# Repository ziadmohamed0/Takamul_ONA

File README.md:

<div align="center">

<br/>
<br/>

# Takamul iQ16 PLC

### Industrial IoT Controller — تكامل للحلول الذكية

<br/>

<br/>

> **Dual-core STM32F405 + ESP32-S3 · Supabase Multi-Tenant Cloud · Modbus RTU · DIN-Rail Mount**
> Designed for water treatment, flow control, and process automation in harsh industrial environments — engineered in Egypt 🇪🇬

</div>

---

## Table of Contents

- [Overview](#overview)
- [Key Features](#key-features)
- [System Architecture](#system-architecture)
- [Hardware](#hardware)
  - [PCB](#pcb--ona_hard)
  - [Mechanical Enclosure — V1](#mechanical-enclosure--v1)
  - [Mechanical Enclosure — V2](#mechanical-enclosure--v2)
- [Firmware](#firmware)
- [Cloud & Connectivity](#cloud--connectivity)
- [Repository Structure](#repository-structure)
- [Getting Started](#getting-started)
- [Supported Instruments](#supported-instruments)

---

## Overview

The **Takamul iQ16** is a compact, DIN-rail mounted industrial PLC built for real-world process automation. It pairs a **STM32F405RGT6** real-time controller — handling deterministic Modbus RTU field communication — with an **ESP32-S3** managing Wi-Fi, MQTT, and secure cloud telemetry via **Supabase Row-Level Security**.

Every unit ships ready to deploy: scan the MAC QR code on the box, link it to your account, and the device self-configures with zero manual setup.

**Built for:**
- Water treatment & desalination plants
- Flow metering systems (Endress+Hauser Promag P300)
- Multi-parameter water quality monitoring (TDS, pressure, temperature, differential)
- VFD pump control automation

---

## Key Features

| | Feature | Detail |
|---|---|---|
| ⚙️ | **Dual-Core Processing** | STM32F405RGT6 (real-time control) + ESP32-S3 (connectivity) |
| 📡 | **Field Protocols** | Modbus RTU × 2 ports (RS-485), bridged to cloud via MQTT |
| 🌊 | **Sensor Inputs** | Flow · Pressure · TDS · Temperature · Differential (5 channels) |
| ⚡ | **Actuator Outputs** | VFD Control × 2 (Variable Frequency Drive) |
| 🔋 | **Power Supply** | 12–24V DC wide-range input, onboard LM2596S regulator |
| 📶 | **Connectivity** | Wi-Fi 802.11 b/g/n, external SMA antenna, USB-C programming |
| ☁️ | **Cloud Backend** | Supabase PostgreSQL + RLS — multi-tenant, per-device data isolation |
| 🔐 | **Security** | JWT auth, RLS policies, NVS encrypted credential storage |
| 💡 | **Status Indicators** | Power · Run · Error · Comms · Wi-Fi (5 onboard LEDs) |
| 📦 | **Form Factor** | DIN-rail 35mm TS35, 3D-printable enclosure included |
| 🔌 | **Programming** | ST-LINK V2 (STM32) + USB-C ESP-IDF (ESP32) |
| 📋 | **Zero-Config** | MAC-based QR pairing — no manual IP or credential entry |

---

## System Architecture

```
┌─────────────────────────────────────────────────────────┐
│                    Field Instruments                     │
│  [Flow Meter]  [Pressure]  [TDS]  [Temp]  [Diff]       │
└──────────────────────┬──────────────────────────────────┘
                       │ Modbus RTU (RS-485)
              ┌────────▼────────┐
              │   STM32F405     │  ← Real-time deterministic control
              │  Modbus Master  │  ← VFD pump output control
              │  FreeRTOS       │
              └────────┬────────┘
                       │ UART (115200 baud)
              ┌────────▼────────┐
              │    ESP32-S3     │  ← Wi-Fi / MQTT / Cloud
              │  WifiManager    │
              │  SupabaseClient │──────────► Supabase Cloud
              │  MqttManager    │              (PostgreSQL + RLS)
              │  TelemetryMgr   │
              │  WebServer      │──────────► Local Config Portal
              │  NVSManager     │
              └─────────────────┘
```

---

## Hardware

### PCB — `ONA_HARD/`

The iQ16 PCB is a **4-layer board** designed in KiCad 7. The stackup separates power planes from signal layers to ensure clean analog sensor readings alongside noisy RS-485 and switching regulator circuits.

| Spec | Value |
|---|---|
| Layers | 4 (F.Cu · In1.Cu · In2.Cu · B.Cu) |
| MCUs | STM32F405RGT6 + ESP32-S3 module |
| Power | LM2596S buck converter, 220µF/35V + 100µF/50V bulk caps |
| RS-485 | Dual Modbus ports (ModBus 1: A/B, ModBus 2: Y/Z) |
| Programming | USB-C (ESP32) + ST-Link header (STM32) |
| Mounting | 4× M3 corner holes for DIN-rail clip assembly |
| Design tool | KiCad 7 |
| Fabrication | Gerber + drill files ready (JLCPCB / PCBWay) |

<table>
  <tr>
    <td align="center" width="50%">
      
      <br/><sub><b>iQ16 — DIN-Rail Mounted</b></sub>
    </td>
    <td align="center" width="50%">
      
      <br/><sub><b>PCB — Top View (3D Render)</b></sub>
    </td>
  </tr>
  <tr>
    <td align="center" width="50%">
      
      <br/><sub><b>PCB — Back View (3D Render)</b></sub>
    </td>
    <td align="center" width="50%">
      
      <br/><sub><b>PCB — KiCad Layout (All Copper Layers)</b></sub>
    </td>
  </tr>
</table>

---

### Mechanical Enclosure — V1

First-generation 3D-printable enclosure. A 4-part snap-fit design tailored for DIN-rail deployment in standard control cabinets.

**Parts:** `Body` · `Face cover` · `Back cover` · `Head cover`

<table>
  <tr>
    <td align="center" width="50%">
      
      <br/><sub><b>V1 — Full Assembly (3D View)</b></sub>
    </td>
    <td align="center" width="50%">
      
      <br/><sub><b>V1 — Front Panel View</b></sub>
    </td>
  </tr>
  <tr>
    <td align="center" width="50%">
      
      <br/><sub><b>V1 — Side Profile</b></sub>
    </td>
    <td align="center" width="50%">
      
      <br/><sub><b>V1 — Internal Layout</b></sub>
    </td>
  </tr>
</table>

All V1 files are in `mechanical/V1/` — CAD source (`.SLDPRT` / `.SLDASM`) and print-ready STLs.

---

### Mechanical Enclosure — V2

Second-generation enclosure with improved cable management, refined connector cutouts, and a modular split body for easier PCB insertion and field service.

**Parts:** `Body` · `Face` · `Back` · `Part1348` (DIN clip assembly)

<table>
  <tr>
    <td align="center" width="50%">
      
      <br/><sub><b>V2 — Full Assembly (3D View)</b></sub>
    </td>
    <td align="center" width="50%">
      
      <br/><sub><b>V2 — Front Panel View</b></sub>
    </td>
  </tr>
  <tr>
    <td align="center" width="50%">
      
      <br/><sub><b>V2 — Side Profile</b></sub>
    </td>
    <td align="center" width="50%">
      
      <br/><sub><b>V2 — Rear Connector Cutouts</b></sub>
    </td>
  </tr>
  <tr>
    <td align="center" colspan="2">
      
      <br/><sub><b>V2 — Exploded View / DIN Clip Detail</b></sub>
    </td>
  </tr>
</table>

All V2 files are in `mechanical/V2/` — CAD source and print-ready STLs.

> **Production-ready STL + OBJ** files (the version shipped with the product) are in `mechanical/sample/cad_v2/`. These include every printable part: `assembly`, `base`, `front_lid`, `top_lid`, `top_connectors`, `bottom_connectors`, `din_clip`, `wifi_module`, `antenna`, `standoff`, `screw_m3x8`.

---

## Firmware

### ESP32-S3 — `ONA_Software/software_v1/` (ESP-IDF v5)

The ESP32 owns all network and cloud operations, acting as a transparent bridge between the STM32 field data and the Supabase backend.

```
Takamul:: namespace
│
├── NVSManager        Flash-backed credential & config storage
├── WifiManager       Auto-connect, reconnect, provisioning fallback
├── SupabaseClient    HTTPS REST client — insert/query with JWT RLS auth
├── TelemetryManager  Periodic sensor data batching & upload
├── MqttManager       Real-time bidirectional command channel
├── UartBridge        UART2 ↔ STM32 framing & protocol (GPIO 16/17)
├── WebServer         Local HTTP config portal for Zero-Config pairing
├── OtaManager        OTA firmware update over HTTPS
└── SleepManager      Deep-sleep power management
```

**Configuring credentials** (via `idf.py menuconfig → Takamul Config`):

```
CONFIG_TAKAMUL_SUPABASE_URL   → your Supabase project URL
CONFIG_TAKAMUL_SUPABASE_KEY   → your anon/service role key
```

### STM32F405 — `ONA_Software/tests/modbus_v2/` (STM32CubeIDE)

Runs a deterministic FreeRTOS Modbus RTU master stack over RS-485. Polls all field instruments on configurable scan cycles and pushes structured telemetry frames to the ESP32 over UART.

### Modbus Mapping — `ONA_Software/tests/modbus_mapping_controll/`

STM32 firmware variant with full register mapping and VFD control logic — maps physical Modbus registers from flow meters, TDS analyzers, and pressure transmitters to structured data objects sent upstream.

---

## Cloud & Connectivity

| Layer | Technology | Purpose |
|---|---|---|
| **Database** | Supabase PostgreSQL | Persistent sensor telemetry & device registry |
| **Security** | Row-Level Security (RLS) | Per-device data isolation, multi-tenant safe |
| **Auth** | JWT tokens | Device identity tied to MAC address |
| **Real-time** | Supabase Realtime | Live dashboard subscriptions |
| **Commands** | MQTT pub/sub | Low-latency actuator control (VFD setpoints) |
| **Local config** | HTTP Web Server | Zero-Config Wi-Fi & account pairing |
| **Pairing** | QR code on box | MAC address → account link, no manual entry |
| **OTA** | HTTPS OTA | Remote firmware updates for ESP32 |

---

## Repository Structure

```
Takamul_ONA/
│
├── ONA_HARD/                          # Hardware design files
│   ├── STM32 & ESP32.kicad_pro       # KiCad 7 project
│   ├── STM32 & ESP32.kicad_sch       # Schematic
│   ├── STM32 & ESP32.kicad_pcb       # PCB layout
│   ├── BOM.xlsx                       # Bill of Materials
│   ├── STM32 & ESP32.pdf             # Schematic PDF export
│   ├── STEP File.step                 # Full assembly STEP
│   ├── top.jpeg / Back.jpeg          # PCB 3D renders
│   └── pcb_Layout.jpeg               # KiCad layout screenshot
│
├── ONA_Software/
│   ├── software_v1/esp32s3_project/  # ESP32-S3 firmware (ESP-IDF v5)
│   │   └── main/
│   │       ├── main.cpp / main.h
│   │       ├── src/
│   │       │   ├── WifiManager.cpp
│   │       │   ├── SupabaseClient.cpp
│   │       │   ├── TelemetryManager.cpp
│   │       │   ├── UartBridge.cpp
│   │       │   ├── WebServer.cpp
│   │       │   ├── MqttManager.cpp
│   │       │   ├── NVSManager.cpp
│   │       │   ├── OtaManager.cpp
│   │       │   └── SleepManager.cpp
│   │       └── inc/                  # Corresponding headers
│   │
│   ├── tests/
│   │   ├── modbus_v2/               # STM32F405 Modbus RTU stack (FreeRTOS)
│   │   ├── modbus_mapping_controll/ # Register mapping & VFD control logic
│   │   ├── STM32_Main/              # STM32F401 base firmware tests
│   │   ├── TestModbus/              # Modbus protocol unit tests
│   │   ├── stm32_master/            # STM32F103 Modbus master prototype
│   │   ├── main_esp32/              # ESP32 (original) integration tests
│   │   └── test_db/                 # ESP32 Supabase integration tests
│   │
│   └── data_sheets/                 # Instrument Modbus documentation
│       ├── Promag_P300_modbus_map.pdf
│       └── CM44x_modbus_map.pdf
│
├── mechanical/
│   ├── V1/                          # Enclosure V1 (SolidWorks + STL)
│   │   ├── CAD/                     # .SLDPRT source files
│   │   ├── STL/                     # Print-ready STL files
│   │   └── PNG/                     # 3D renders (3D, S1, S2, S3)
│   │
│   ├── V2/                          # Enclosure V2 (SolidWorks + STL)
│   │   ├── CAD/                     # .SLDPRT source files
│   │   ├── STL/                     # Print-ready STL files
│   │   └── PNG/                     # 3D renders (3D, S1, S2, S3, S4)
│   │
│   └── sample/                      # Production-ready assets
│       ├── cad_v2/                  # Final STL + OBJ (all parts)
│       ├── docs/
│       │   ├── bom_v2.csv
│       │   └── takamul_iq16_drawing_pack.pdf
│       ├── case.jpeg                # Mounted enclosure photo
│       └── pkg.jpeg                 # Product packaging render
│
└── docs/
    └── images/                      # README assets
```

---

## Getting Started

### What's in the Box

- Takamul iQ16 Controller Unit
- Quick Start Guide
- USB-C Programming Cable
- ST-LINK V2 Programmer

### Prerequisites

| Tool | Purpose | Link |
|---|---|---|
| ESP-IDF v5 | ESP32-S3 firmware build | [docs.espressif.com](https://docs.espressif.com/projects/esp-idf/en/latest/) |
| STM32CubeIDE | STM32 firmware build & flash | [st.com](https://www.st.com/en/development-tools/stm32cubeide.html) |
| KiCad 7 | PCB schematic & layout | [kicad.org](https://www.kicad.org) |
| ST-LINK V2 | STM32 programmer (included) | — |

### Flash ESP32 Firmware

```bash
cd ONA_Software/software_v1/esp32s3_project
idf.py set-target esp32s3
idf.py menuconfig        # Takamul Config → set Supabase URL & key
idf.py build flash monitor
```

### Flash STM32 Firmware

```bash
# Open in STM32CubeIDE
File → Open Projects from File System → ONA_Software/tests/modbus_v2/

# Build & flash via ST-LINK V2
Project → Build (Ctrl+B)
Run → Debug (connects via ST-LINK header)
```

### Open PCB in KiCad

```bash
kicad ONA_HARD/
# Open "STM32 & ESP32.kicad_pro" → Schematic Editor or PCB Editor
```

### Print the Enclosure (V2 — Production)

All production STL files are in `mechanical/sample/cad_v2/`. Recommended print order:

1. `base.stl` — main enclosure body
2. `din_clip.stl` — DIN-rail clip
3. `front_lid.stl` — front panel
4. `top_lid.stl` — top cover
5. `top_connectors.stl` + `bottom_connectors.stl` — terminal cutout panels
6. `standoff.stl` × 4 — PCB standoffs
7. `wifi_module.stl` — ESP32 module retainer
8. `antenna.stl` — SMA antenna bracket

> **Recommended settings:** PLA or PETG, 0.2mm layer height, 4 perimeters, 30% infill.

---

## Supported Instruments

| Instrument | Protocol | Datasheet |
|---|---|---|
| Endress+Hauser Promag P300 | Modbus RTU | `ONA_Software/data_sheets/Promag_P300_modbus_map.pdf` |
| Endress+Hauser Liquiline CM44x | Modbus RTU | `ONA_Software/data_sheets/CM44x_modbus_map.pdf` |
| Generic TDS Sensor | Analog / RS-485 | — |
| Generic Pressure Transmitter | 4–20 mA | — |
| Generic Temperature Sensor | Analog | — |

---

<div align="center">

<br/>

**Takamul Smart Solutions — تكامل للحلول الذكية**

*Industrial IoT, engineered in Egypt 🇪🇬*

<br/>

</div>

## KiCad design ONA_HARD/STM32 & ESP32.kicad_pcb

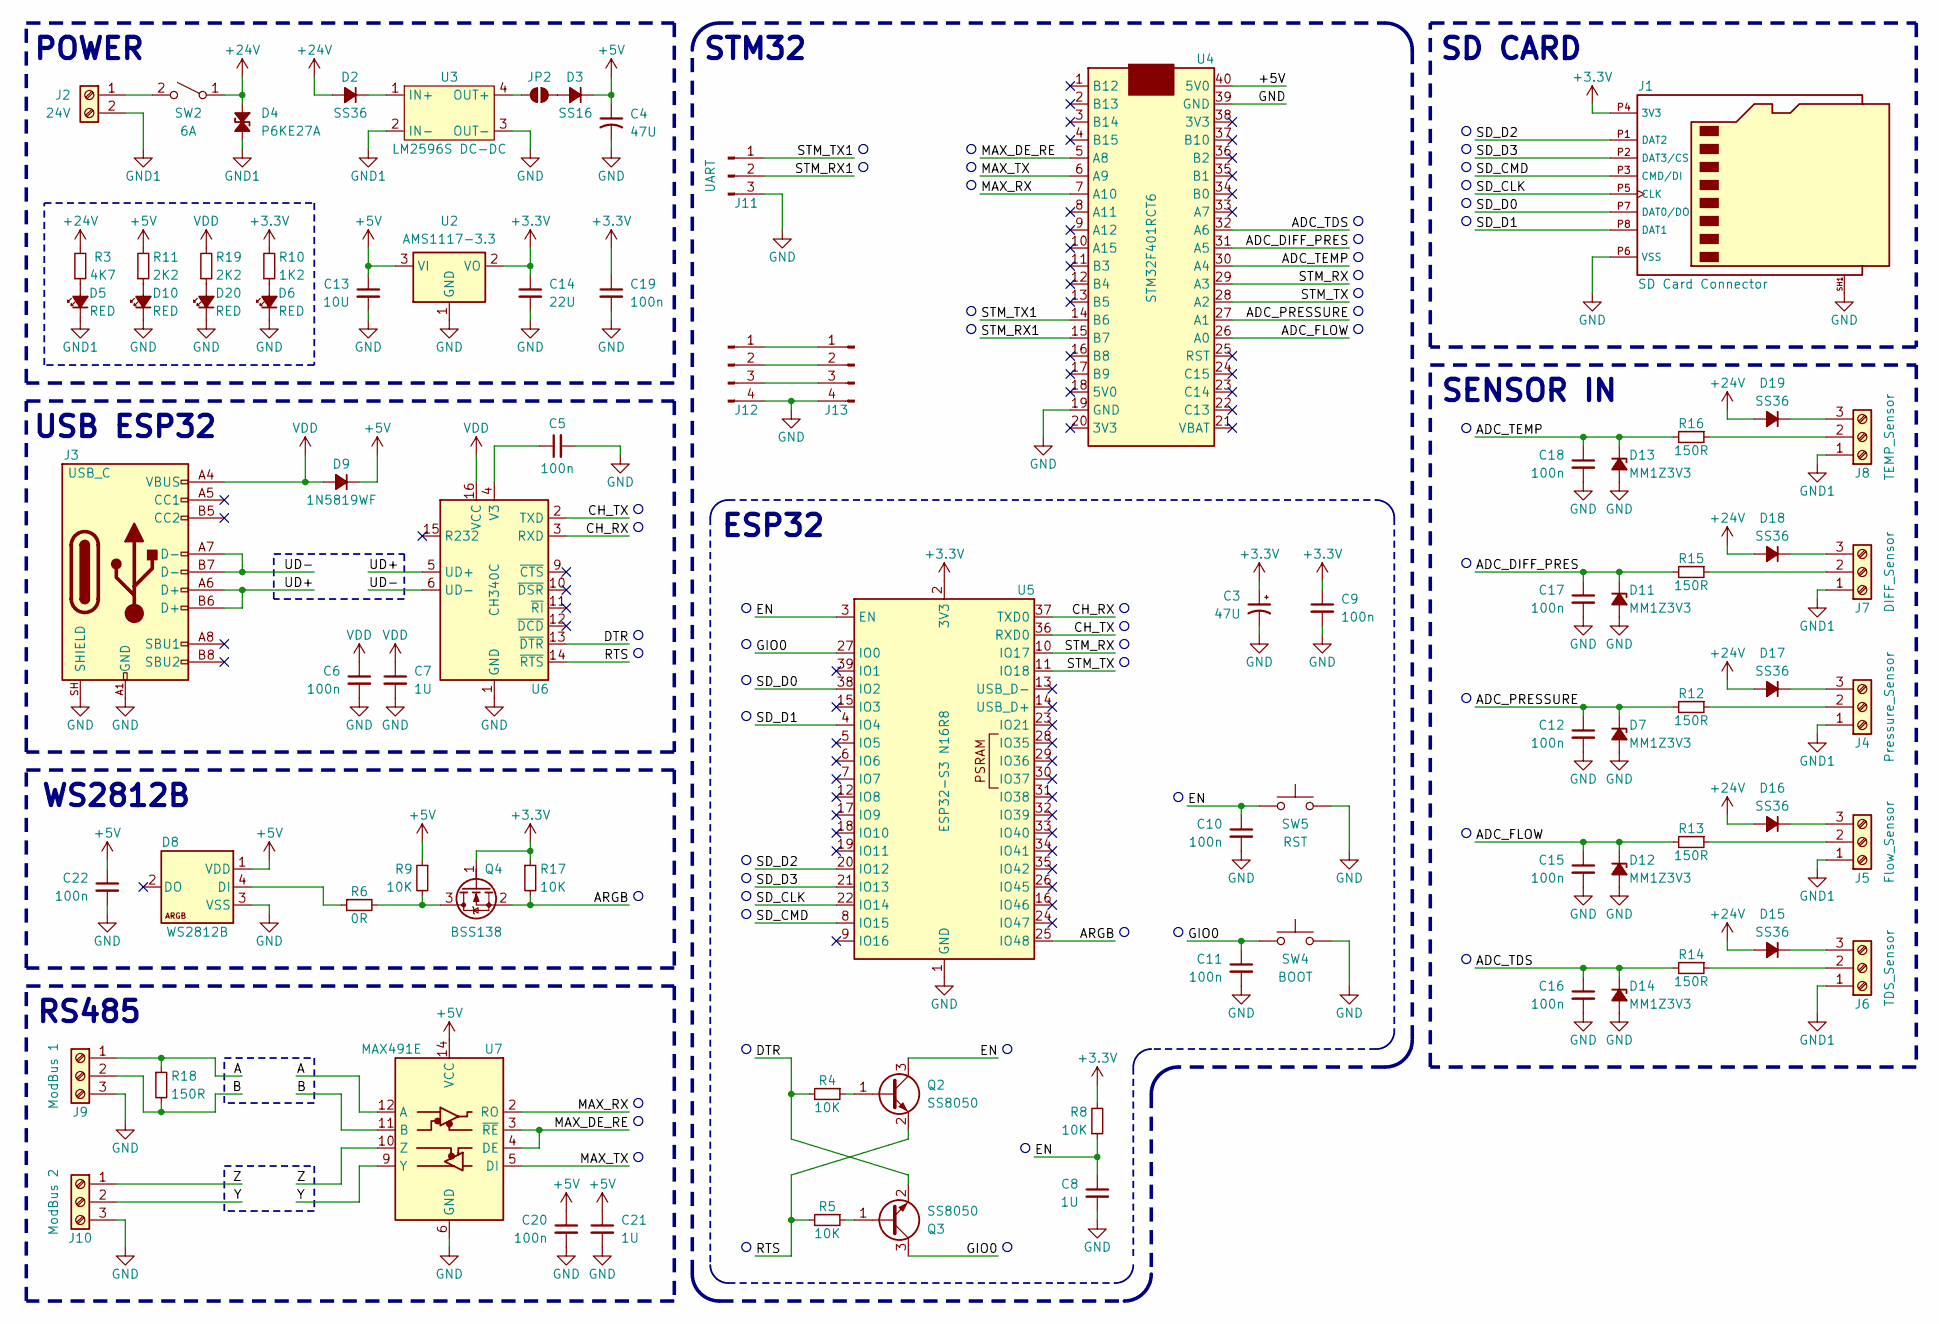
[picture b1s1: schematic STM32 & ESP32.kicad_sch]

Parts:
C3: 47U; CP_EIA-3528-12_Kemet-T_HandSolder
C4: 47U; CP_Radial_D6.3mm_P2.50mm
C5, C6, C9, C10, C11, C12, C15, C16, C17, C18, C19, C20, C22: 100n; C_0805_2012Metric_Pad1.18x1.45mm_HandSolder
C7, C8, C21: 1U; C_0805_2012Metric_Pad1.18x1.45mm_HandSolder
C13: 10U; C_0805_2012Metric_Pad1.18x1.45mm_HandSolder
C14: 22U; C_0805_2012Metric_Pad1.18x1.45mm_HandSolder
D2, D15, D16, D17, D18, D19: SS36; D_SMA
D3: SS16; D_SMA
D4: P6KE27A; D_DO-15_P12.70mm_Horizontal
D5, D6, D10, D20: RED; LED_0805_2012Metric_Pad1.15x1.40mm_HandSolder
D7, D11, D12, D13, D14: MM1Z3V3; D_SOD-123
D8: WS2812B; LED_WS2812B-Mini_PLCC4_3.5x3.5mm
D9: 1N5819WF; D_SOD-123F
J1: SD Card Connector; SD Card Connector GCT_MEM2075
J2: 24V; Pluggable Terminal 2P P5.08mm
J3: USB_C; USB_C_Receptacle_G-Switch_GT-USB-7010ASV
J4: Pressure_Sensor; Pluggable Terminal 3P P5.08mm
J5: Flow_Sensor; Pluggable Terminal 3P P5.08mm
J6: TDS_Sensor; Pluggable Terminal 3P P5.08mm
J7: DIFF_Sensor; Pluggable Terminal 3P P5.08mm
J8: TEMP_Sensor; Pluggable Terminal 3P P5.08mm
J9: ModBus 1; Pluggable Terminal 3P P5.08mm
J10: ModBus 2; Pluggable Terminal 3P P5.08mm
J11: UART; PinHeader_1x03_P2.54mm_Vertical
J12: Conn_01x04_Pin; PinHeader_1x04_P2.54mm_Vertical
J13: PinHeader_1x04_P2.54mm_Vertical
JP2: SolderJumper_2_Open; SolderJumper-2_P1.3mm_Open_TrianglePad1.0x1.5mm
Q2, Q3: SS8050; SOT-23
Q4: BSS138; SOT-23
R3: 4K7; R_0805_2012Metric_Pad1.20x1.40mm_HandSolder
R4, R5, R8, R9, R17: 10K; R_0805_2012Metric_Pad1.20x1.40mm_HandSolder
R6: 0R; SolderJumper-2_P1.3mm_Open_TrianglePad1.0x1.5mm
R10: 1K2; R_0805_2012Metric_Pad1.20x1.40mm_HandSolder
R11, R19: 2K2; R_0805_2012Metric_Pad1.20x1.40mm_HandSolder
R12, R13, R14, R15, R16, R18: 150R; R_0805_2012Metric_Pad1.20x1.40mm_HandSolder
SW2: 6A; SolderWire-0.5sqmm_1x02_P4.8mm_D0.9mm_OD2.3mm
SW4: BOOT; SW_SPST_PTS647_Sx50
SW5: RST; SW_SPST_PTS647_Sx50
U2: AMS1117-3.3; SOT-223-3_TabPin2
U3: LM2596S DC-DC; LM2596S DC-DC Converter 3A
U4: STM32F401RCT6; Black Pill STM32F401RCT6
U5: ESP32-S3 N16R8; ESP32-S3-WROOM-1
U6: CH340C; SOIC-16_3.9x9.9mm_P1.27mm
U7: MAX491E; SOIC-14_3.9x8.7mm_P1.27mm

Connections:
+3.3V: C3.1, C9.1, C14.1, C19.1, J1.P4 (3V3), Q4.1 (G), R8.2, R10.2, R17.1, U2.2 (VO), U5.2 (3V3)
+5V: C4.1, C13.1, C20.1, C21.1, C22.1, D3.1 (K), D8.1 (VDD), D9.1 (K), R9.1, R11.2, U2.3 (VI), U4.40 (5V0), U7.14 (VCC)
+24V: D2.2 (A), D4.1 (A1), D15.2 (A), D16.2 (A), D17.2 (A), D18.2 (A), D19.2 (A), R3.2, SW2.1 (A)
/A: J9.1, R18.1, U7.12 (A)
/ADC_DIFF_PRES: C17.1, D11.1 (K), R15.2, U4.31 (A5)
/ADC_FLOW: C15.1, D12.1 (K), R13.2, U4.26 (A0)
/ADC_PRESSURE: C12.1, D7.1 (K), R12.2, U4.27 (A1)
/ADC_TDS: C16.1, D14.1 (K), R14.2, U4.32 (A6)
/ADC_TEMP: C18.1, D13.1 (K), R16.2, U4.30 (A4)
/ARGB: Q4.2 (S), R17.2, U5.25 (IO48)
/B: J9.2, R18.2, U7.11 (B)
/CH_RX: U5.37 (TXD0), U6.3 (RXD)
/CH_TX: U5.36 (RXD0), U6.2 (TXD)
/DTR: Q3.2 (E), R4.2, U6.13 (~DTR)
/EN: C8.1, C10.1, Q2.3 (C), R8.1, SW5.2, U5.3 (EN)
/GIO0: C11.1, Q3.3 (C), SW4.2, U5.27 (IO0)
/MAX_DE_RE: U4.5 (A8), U7.3 (~RE), U7.4 (DE)
/MAX_RX: U4.7 (A10), U7.2 (RO)
/MAX_TX: U4.6 (A9), U7.5 (DI)
/RTS: Q2.2 (E), R5.2, U6.14 (~RTS)
/SD_CLK: J1.P5 (CLK), U5.22 (IO14)
/SD_CMD: J1.P3 (CMD/DI), U5.8 (IO15)
/SD_D0: J1.P7 (DAT0/DO), U5.38 (IO2)
/SD_D1: J1.P8 (DAT1), U5.4 (IO4)
/SD_D2: J1.P1 (DAT2), U5.20 (IO12)
/SD_D3: J1.P2 (DAT3/CS), U5.21 (IO13)
/STM_RX: U4.29 (A3), U5.10 (IO17)
/STM_RX1: J11.2, U4.15 (B7)
/STM_TX: U4.28 (A2), U5.11 (IO18)
/STM_TX1: J11.1, U4.14 (B6)
/UD+: J3.A6 (D+), J3.B6 (D+), U6.5 (UD+)
/UD-: J3.A7 (D-), J3.B7 (D-), U6.6 (UD-)
/Y: J10.2, U7.9 (Y)
/Z: J10.1, U7.10 (Z)
GND: C3.2, C4.2, C5.2, C6.2, C7.2, C8.2, C9.2, C10.2, C11.2, C12.2, C13.2, C14.2, C15.2, C16.2, C17.2, C18.2, C19.2, C20.2, C21.2, C22.2, D6.1 (K), D7.2 (A), D8.3 (VSS), D10.1 (K), D11.2 (A), D12.2 (A), D13.2 (A), D14.2 (A), D20.1 (K), J1.P6 (VSS), J1.SH1, J1.SH2 (SHIELD), J1.SH3 (SHIELD), J1.SH4 (SHIELD), J3.A1 (GND), J3.A12 (GND), J3.B1 (GND), J3.B12 (GND), J3.SH (SHIELD), J9.3, J10.3, J11.3, J12.4, J13.4, SW4.1, SW5.1, U2.1 (GND), U3.3 (OUT-), U4.19 (GND), U4.39 (GND), U5.1 (GND), U5.40 (GND), U5.41 (GND), U6.1 (GND), U7.6 (GND), U7.7 (GND)
GND1: D4.2 (A2), D5.1 (K), J2.2, J4.1, J5.1, J6.1, J7.1, J8.1, U3.2 (IN-)
unnamed: D2.1 (K), U3.1 (IN+)
unnamed: D3.2 (A), JP2.2 (B)
unnamed: D5.2 (A), R3.1
unnamed: D6.2 (A), R10.1
unnamed: D8.4 (DI), R6.1
unnamed: D10.2 (A), R11.1
unnamed: D15.1 (K), J6.3
unnamed: D16.1 (K), J5.3
unnamed: D17.1 (K), J4.3
unnamed: D18.1 (K), J7.3
unnamed: D19.1 (K), J8.3
unnamed: D20.2 (A), R19.1
unnamed: J2.1, SW2.2 (B)
unnamed: J4.2, R12.1
unnamed: J5.2, R13.1
unnamed: J6.2, R14.1
unnamed: J7.2, R15.1
unnamed: J8.2, R16.1
unnamed: J12.1, J13.1
unnamed: J12.2, J13.2
unnamed: J12.3, J13.3
unnamed: JP2.1 (A), U3.4 (OUT+)
unnamed: Q2.1 (B), R4.1
unnamed: Q3.1 (B), R5.1
unnamed: Q4.3 (D), R6.2, R9.2
unnamed: C5.1, U6.4 (V3)
VDD: C6.1, C7.1, D9.2 (A), J3.A4 (VBUS), J3.A9 (VBUS), J3.B4 (VBUS), J3.B9 (VBUS), R19.2, U6.16 (VCC)

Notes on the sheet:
SD CARD
USB ESP32
POWER
SENSOR IN
ESP32
RS485
STM32
WS2812B

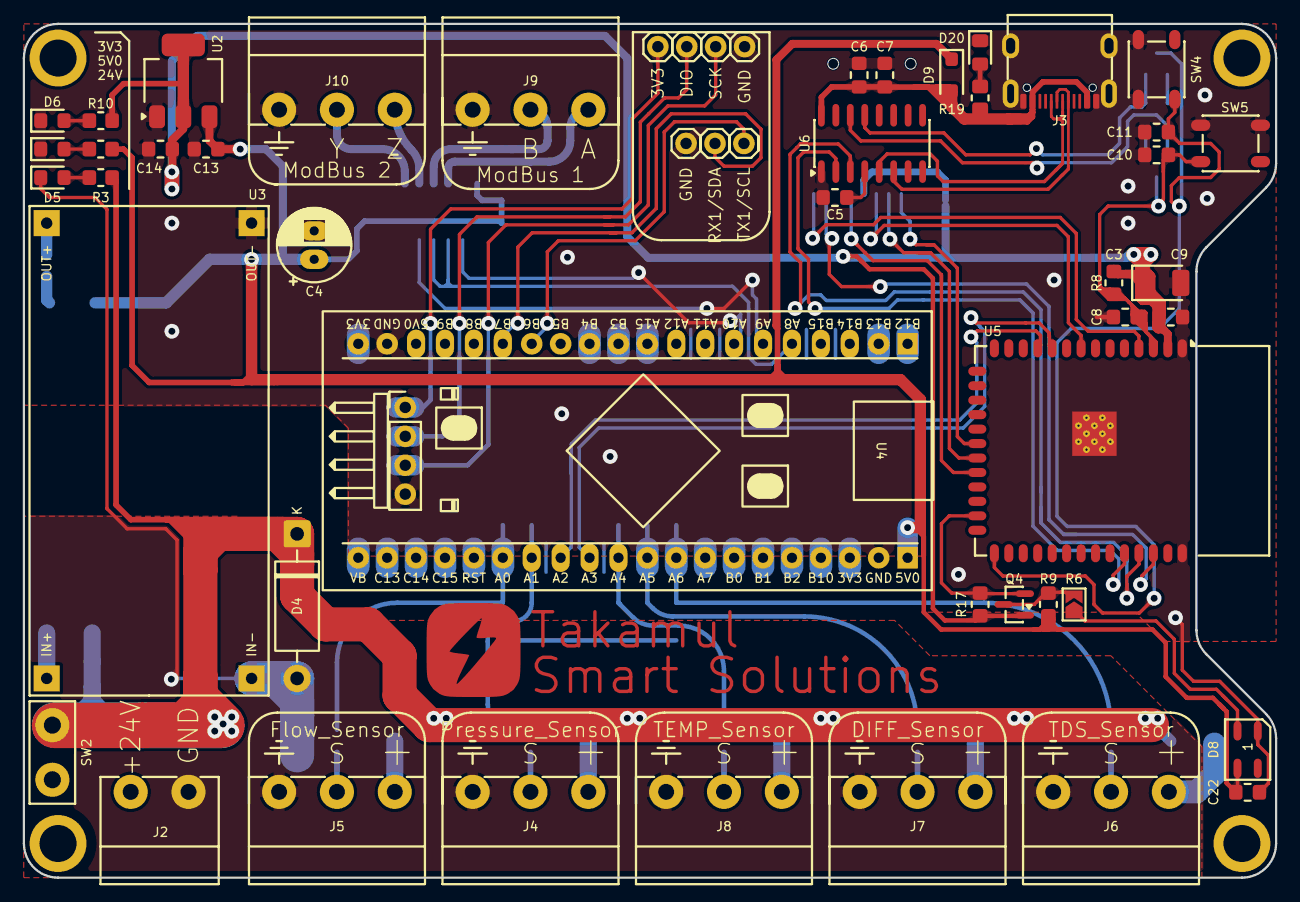
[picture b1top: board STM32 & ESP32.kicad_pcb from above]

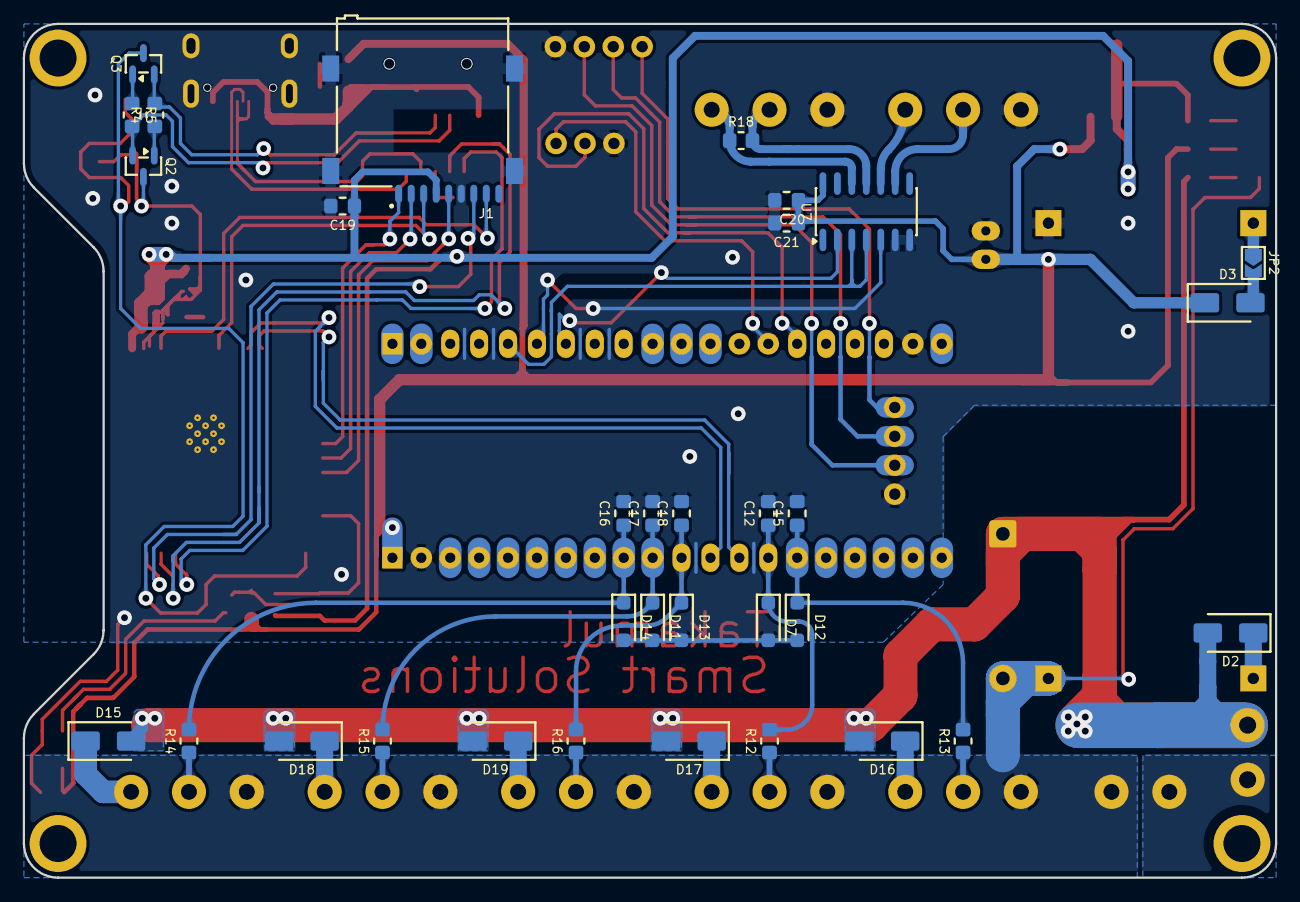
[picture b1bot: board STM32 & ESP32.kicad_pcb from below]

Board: 2 copper layers, 110.0 x 75.0 mm, 81 parts (33 on the bottom side), 63 nets.

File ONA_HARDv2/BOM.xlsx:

Ref | Value | Footpint | Qty | Shop | Link
C14 | 22U | Capacitor_SMD:C_0805_2012Metric_Pad1.18x1.45mm_HandSolder | 1 | Makers | https://makerselectronics.com/product/multilayer-ceramic-cap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
D2, D15-D19 | SS36 | Diode_SMD:D_SMA | 6 | Makers | https://makerselectronics.com/product/ss36-sma-schottky-barr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
D3 | SS16 | Diode_SMD:D_SMA | 1 | Makers | https://makerselectronics.com/product/ss16-sma-schottky-barr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
D4 | P6KE27A | Diode_THT:D_DO-15_P12.70mm_Horizontal | 1 | Makers | https://makerselectronics.com/product/esd-suppressors-tvs-di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
D5, D6, D10 | LED_RED | LED_SMD:LED_0805_2012Metric_Pad1.15x1.40mm_HandSolder | 3 | Makers | https://makerselectronics.com/product/smd-led-0805/
D7, D11-D14 | MM1Z3V3 | Diode_SMD:D_SOD-123 | 5 | Makers | https://makerselectronics.com/product/mm1z3v3-w3-zener-diode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
D9 | 1N5819WF | Diode_SMD:D_SOD-123F | 1 | Makers | https://makerselectronics.com/product/1n5819wf-sl-40v-600mv1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
J2 | Pluggable Terminal 2P | abjad:Pluggable Terminal 2P P5.08mm | 1 | Makers | https://makerselectronics.com/product/terminal-block-kf2edgr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
J3 | USB_TYPEC_12P | Connector_USB:USB_C_Receptacle_G-Switch_GT-USB-7010ASV | 1 | Makers | https://makerselectronics.com/product/smd-usb-female-connect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
J4-J10 | Pluggable Terminal 3P | abjad:Pluggable Terminal 3P P5.08mm | 7 | Makers | https://makerselectronics.com/product/terminal-block-kf2edgr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
J11 | UART | Connector_PinHeader_2.54mm:PinHeader_1x03_P2.54mm_Vertical | 1 | Makers | https://makerselectronics.com/product/pin-headers-male-2-54m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
Q2, Q3 | SS8050 | Package_TO_SOT_SMD:SOT-23 | 2 | Makers | https://makerselectronics.com/product/ss8050-y1-bipolar-tran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
R3 | 4K7 | Resistor_SMD:R_0805_2012Metric_Pad1.20x1.40mm_HandSolder | 1 | Makers | https://makerselectronics.com/product/chip-resistor-smd-4-7k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
R4, R5, R8, R9, R17 | 10K | Resistor_SMD:R_0805_2012Metric_Pad1.20x1.40mm_HandSolder | 5 | Makers | https://makerselectronics.com/product/chip-resistor-smd-10k%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
R10 | 1K2 | Resistor_SMD:R_0805_2012Metric_Pad1.20x1.40mm_HandSolder | 1 | Makers | https://makerselectronics.com/product/chip-resistor-smd-1-2k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
R11 | 2K2 | Resistor_SMD:R_0805_2012Metric_Pad1.20x1.40mm_HandSolder | 1 | Makers | https://makerselectronics.com/product/chip-resistor-smd-2-2k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
R12-R16, R18 | 150R | Resistor_SMD:R_0805_2012Metric_Pad1.20x1.40mm_HandSolder | 6 | Makers | https://makerselectronics.com/product/chip-resistor-smd-150%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
SW2 | SW_6A | abjad:SW-KCD-6A | 1 | Makers | https://makerselectronics.com/product/on-off-red-switch-3-pi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
U6 | CH340C | Package_SO:SOIC-16_3.9x9.9mm_P1.27mm | 1 | Makers | https://makerselectronics.com/product/ch340c-smd-ic-transcei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
U3 | LM2596S DC-DC | abjad:LM2596S DC-DC Converter 3A | 1 | Makers | https://makerselectronics.com/product/lm2596hvs-dc-dc-buck-c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
U4 | STM32F401RCT6 | abjad:Black Pill STM32F401RCT6 | 1 | Makers | https://makerselectronics.com/product/stm32f401rct6-stm32-de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
U5 | ESP32-S3 N16R8 | RF_Module:ESP32-S3-WROOM-1 | 1 | Uge | https://uge-one.com/product/esp32-s3-n16r8-high-performance-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
U7 | MAX491E | Package_SO:SOIC-14_3.9x8.7mm_P1.27mm | 1 | Makers | https://makerselectronics.com/product/max491esd-transceiver-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
J1 | SD Card Connector | abjad:SD Card Connector GCT_MEM2075 | 1 | UGE | https://uge-one.com/product/microsd-memory-sd-card-socket-pc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
D8 | WS2812B | LED_SMD:LED_WS2812B-Mini_PLCC4_3.5x3.5mm | 1 | UGE | https://uge-one.com/product/ws2812b-programmable-rgb-led-chi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
Q4 | BSS138 | Package_TO_SOT_SMD:SOT-23 | 1 | Ram | https://www.ram-e-shop.com/shop/smd-bss138-smd-bss138-8694
SW4, SW5 | SW | Button_Switch_SMD:SW_SPST_PTS647_Sx50 | 2 | Uge | https://uge-one.com/product/smd-mini-pushbutton-switch-4p-4-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
U2 | AMS1117-3.3 | Package_TO_SOT_SMD:SOT-223-3_TabPin2 | 1 | Ram | https://www.ram-e-shop.com/shop/lt1117-3-3v-ams1117-3-3v-6628

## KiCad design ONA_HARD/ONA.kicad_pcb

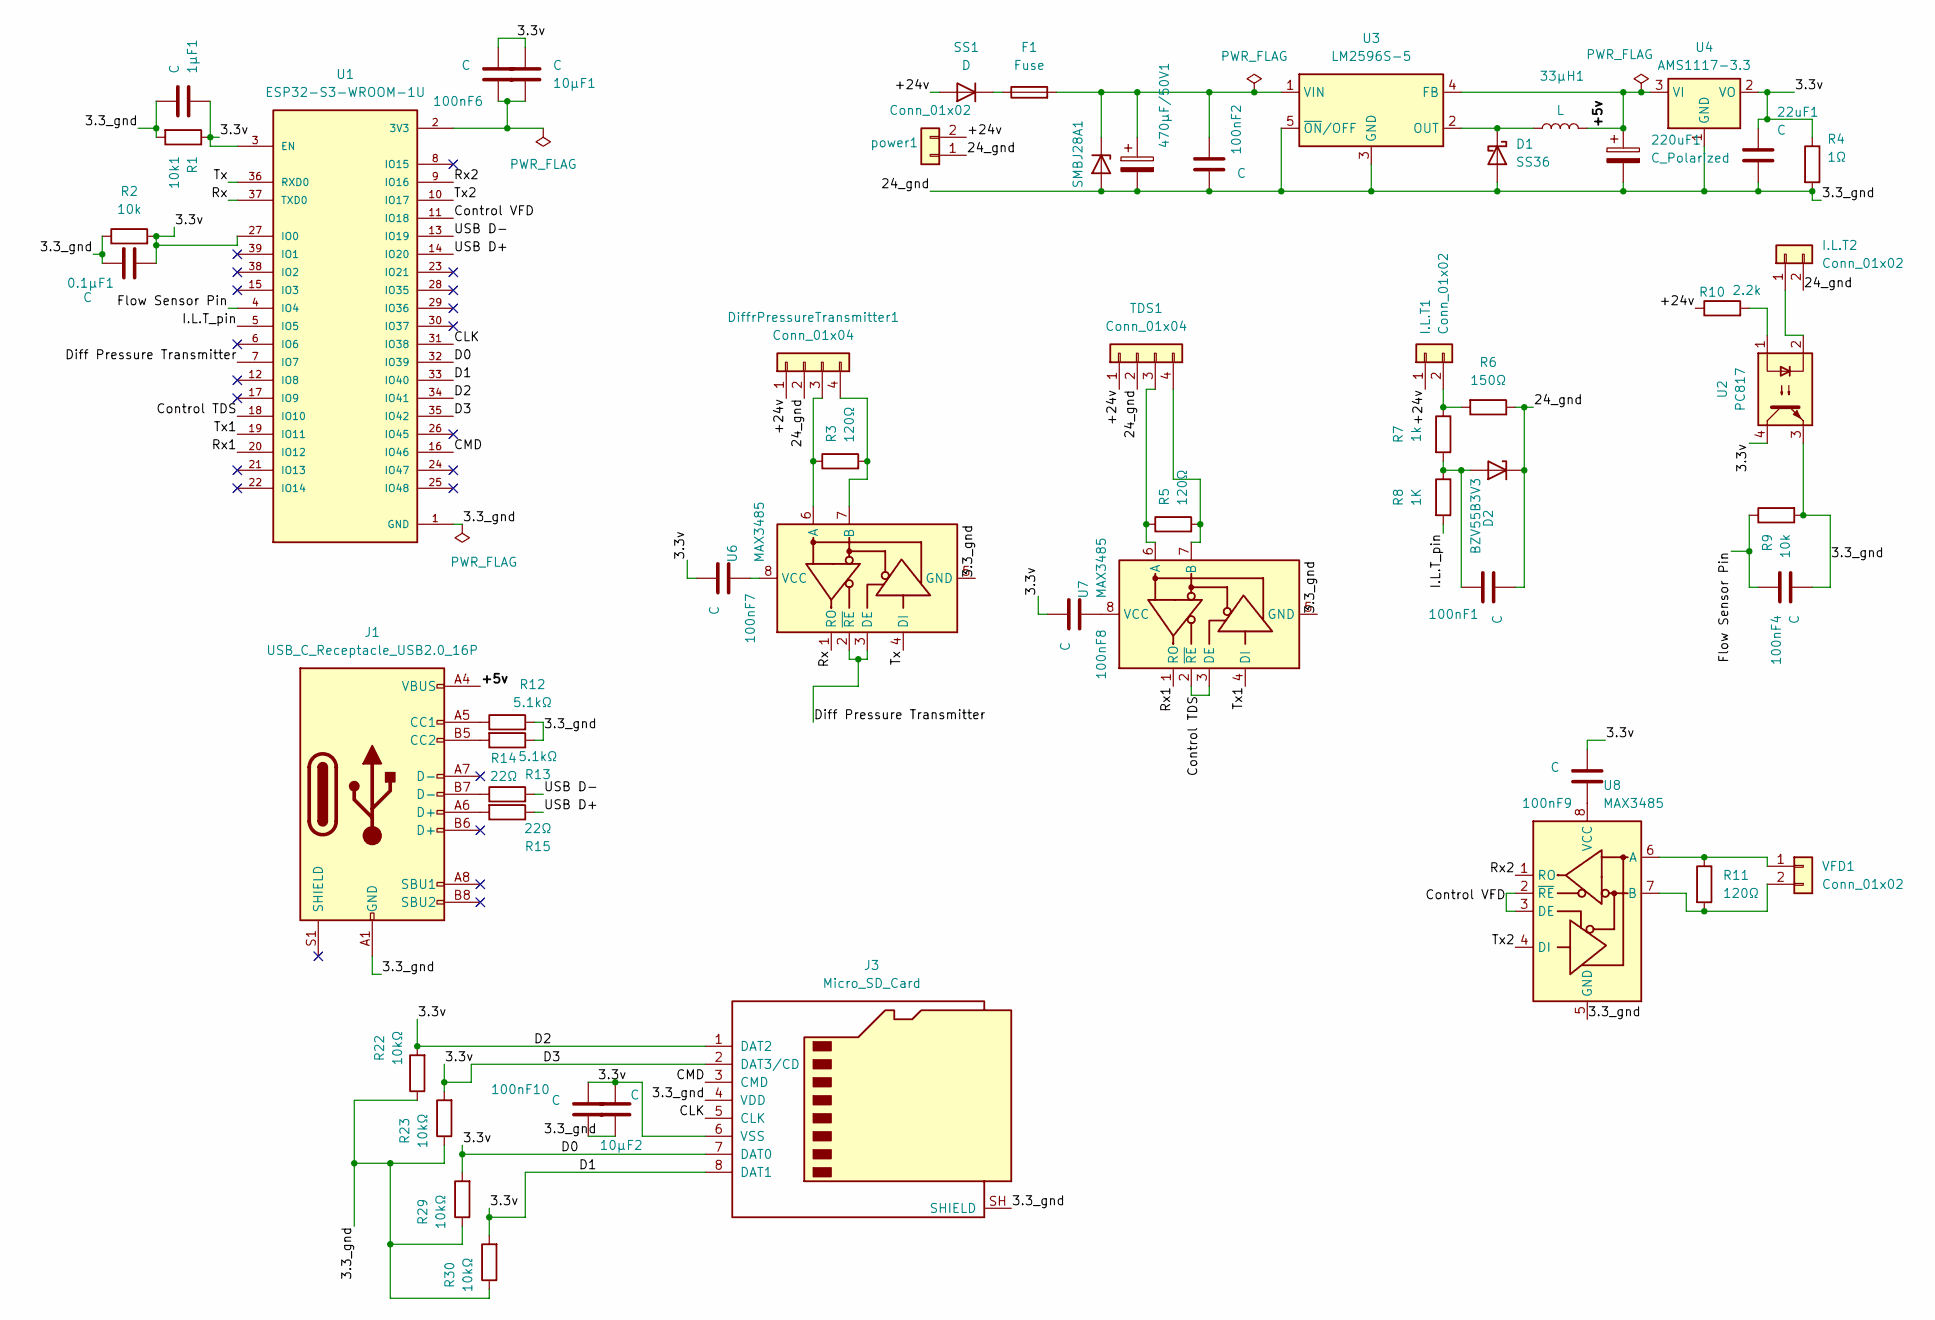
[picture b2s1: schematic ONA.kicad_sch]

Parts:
0.1µF1, 1μF1, 10μF1, 10μF2, 22uF1, 100nF1, 100nF2, 100nF4, 100nF6, 100nF7, 100nF8, 100nF9, 100nF10: C; C_0805_2012Metric
33µH1: L; L_Bourns_SRR1260
220uF1: C_Polarized; CP_Elec_6.3x7.7
470µF/50V1: C_Polarized; CP_Elec_10x10.5
D1: SS36; D_SMC
D2: BZV55B3V3; D_MiniMELF
DiffrPressureTransmitter1: Conn_01x04; TerminalBlock_Phoenix_PT-1,5-4-5.0-H_1x04_P5.00mm_Horizontal
F1: Fuse; Fuse_0805_2012Metric
I.L.T1, I.L.T2: Conn_01x02; TerminalBlock_Phoenix_PT-1,5-2-5.0-H_1x02_P5.00mm_Horizontal
J1: USB_C_Receptacle_USB2.0_16P; USB_C_Receptacle_HRO_TYPE-C-31-M-12
J3: Micro_SD_Card; microSD_HC_Hirose_DM3D-SF
R1: 10k1; R_0805_2012Metric
R2, R9: 10k; R_0805_2012Metric
R3, R5, R11: 120Ω; R_0805_2012Metric
R4: 1Ω; R_0805_2012Metric
R6: 150Ω; R_0805_2012Metric
R7: 1k; R_0805_2012Metric
R8: 1K; R_0805_2012Metric
R10: 2.2k; R_0805_2012Metric
R12, R13: 5.1kΩ; R_0805_2012Metric
R14, R15: 22Ω; R_0805_2012Metric
R22, R23, R29, R30: 10kΩ; R_0805_2012Metric
SMBJ28A1: PTVS5V0Z1USK; D_SMB
SS1: D; D_SMA
TDS1: Conn_01x04; TerminalBlock_Phoenix_PT-1,5-4-5.0-H_1x04_P5.00mm_Horizontal
U1: ESP32-S3-WROOM-1U; XCVR_ESP32-S3-WROOM-1U; PARTREV v0.6
U2: PC817; SMDIP-4_W7.62mm
U3: LM2596S-5; TO-263-5_TabPin3
U4: AMS1117-3.3; SOT-223-3_TabPin2
U6, U7, U8: MAX3485; SOIC-8_3.9x4.9mm_P1.27mm
VFD1: Conn_01x02; TerminalBlock_Phoenix_PT-1,5-2-5.0-H_1x02_P5.00mm_Horizontal
power1: Conn_01x02; TerminalBlock_Phoenix_PT-1,5-2-5.0-H_1x02_P5.00mm_Horizontal

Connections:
/3.3v: 0.1µF1.1, 1μF1.1, 10μF1.2, 10μF2.2, 22uF1.1, 100nF6.2, 100nF7.2, 100nF8.2, 100nF9.2, 100nF10.2, J3.1 (DAT2), J3.2 (DAT3/CD), J3.6 (VSS), J3.7 (DAT0), J3.8 (DAT1), R1.1, R2.2, R4.1, R22.2, R23.2, R29.2, R30.2, U1.3 (EN), U1.27 (IO0), U1.32 (IO39), U1.33 (IO40), U1.34 (IO41), U1.35 (IO42), U2.4, U4.2 (VO)
/+5v: 33µH1.2, 220uF1.1, J1.A4 (VBUS), J1.A9 (VBUS), J1.B4 (VBUS), J1.B9 (VBUS), U3.4 (FB), U4.3 (VI)
/+24v: DiffrPressureTransmitter1.1, I.L.T1.1, R10.1, SS1.2 (A), TDS1.1, power1.2
/CLK: J3.5 (CLK), U1.31 (IO38)
/CMD: J3.3 (CMD), U1.16 (IO46)
/Control TDS: U1.18 (IO10), U7.2 (~RE), U7.3 (DE)
/Control VFD: U1.11 (IO18), U8.2 (~RE), U8.3 (DE)
/Diff Pressure Transmitter: U1.7 (IO7), U6.2 (~RE), U6.3 (DE)
/Flow Sensor Pin: 100nF4.1, R9.1, U1.4 (IO4)
/I.L.T_pin: R8.2, U1.5 (IO5)
/Rx: U1.37 (TXD0), U6.1 (RO)
/Rx1: U1.20 (IO12), U7.1 (RO)
/Rx2: U1.9 (IO16), U8.1 (RO)
/Tx: U1.36 (RXD0), U6.4 (DI)
/Tx1: U1.19 (IO11), U7.4 (DI)
/Tx2: U1.10 (IO17), U8.4 (DI)
/USB D+: R15.1, U1.14 (IO20)
/USB D-: R14.2, U1.13 (IO19)
GND: 0.1µF1.2, 1μF1.2, 10μF2.1, 22uF1.2, 100nF1.2, 100nF2.2, 100nF4.2, 100nF10.1, 220uF1.2, 470µF/50V1.2, D1.2 (A), D2.1 (K), DiffrPressureTransmitter1.2, I.L.T2.2, J1.A1 (GND), J1.A12 (GND), J1.B1 (GND), J1.B12 (GND), J3.4 (VDD), J3.SH (SHIELD), R1.2, R2.1, R4.2, R6.1, R9.2, R12.2, R13.1, R22.1, R23.1, R29.1, R30.1, SMBJ28A1.2 (A), TDS1.2, U1.1 (GND), U1.40 (GND), U1.41_1 (GND), U1.41_2 (GND), U1.41_3 (GND), U1.41_4 (GND), U1.41_5 (GND), U1.41_6 (GND), U1.41_7 (GND), U1.41_8 (GND), U1.41_9 (GND), U2.3, U3.3 (GND), U3.5 (~ON/OFF), U4.1 (GND), U6.5 (GND), U7.5 (GND), U8.5 (GND), power1.1
unnamed: 33µH1.1, D1.1 (K), U3.2 (OUT)
unnamed: 100nF1.1, D2.2 (A), R7.2, R8.1
unnamed: DiffrPressureTransmitter1.3, R3.1, U6.6 (A)
unnamed: DiffrPressureTransmitter1.4, R3.2, U6.7 (B)
unnamed: I.L.T1.2, R6.2, R7.1
unnamed: I.L.T2.1, U2.2
unnamed: J1.A5 (CC1), R12.1
unnamed: J1.B5 (CC2), R13.2
unnamed: J1.A6 (D+), R15.2
unnamed: J1.B7 (D-), R14.1
unnamed: R10.2, U2.1
unnamed: 100nF2.1, 470µF/50V1.1, F1.2, SMBJ28A1.1 (K), U3.1 (VIN)
unnamed: F1.1, SS1.1 (K)
unnamed: R5.1, TDS1.3, U7.6 (A)
unnamed: R5.2, TDS1.4, U7.7 (B)
unnamed: 10μF1.1, 100nF6.1, U1.2 (3V3)
unnamed: 100nF7.1, U6.8 (VCC)
unnamed: 100nF8.1, U7.8 (VCC)
unnamed: R11.1, U8.6 (A), VFD1.1
unnamed: R11.2, U8.7 (B), VFD1.2
unnamed: 100nF9.1, U8.8 (VCC)

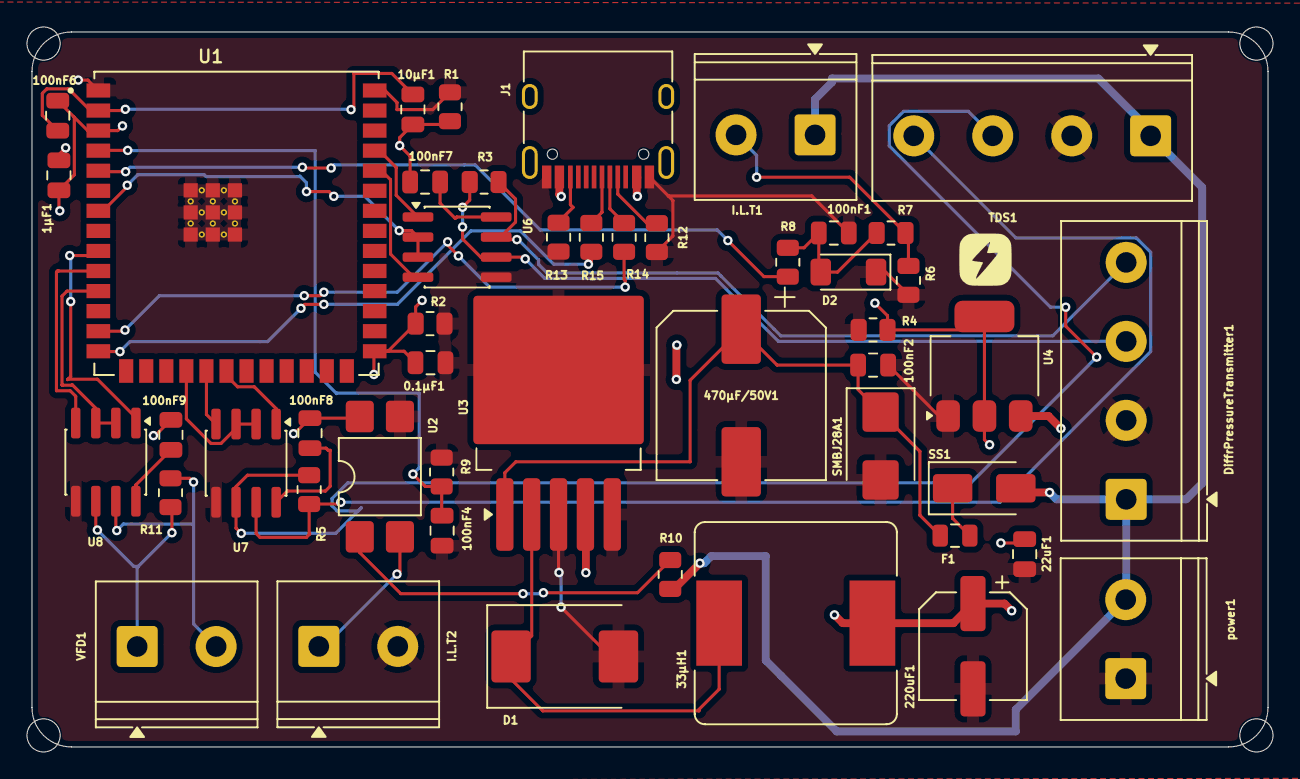
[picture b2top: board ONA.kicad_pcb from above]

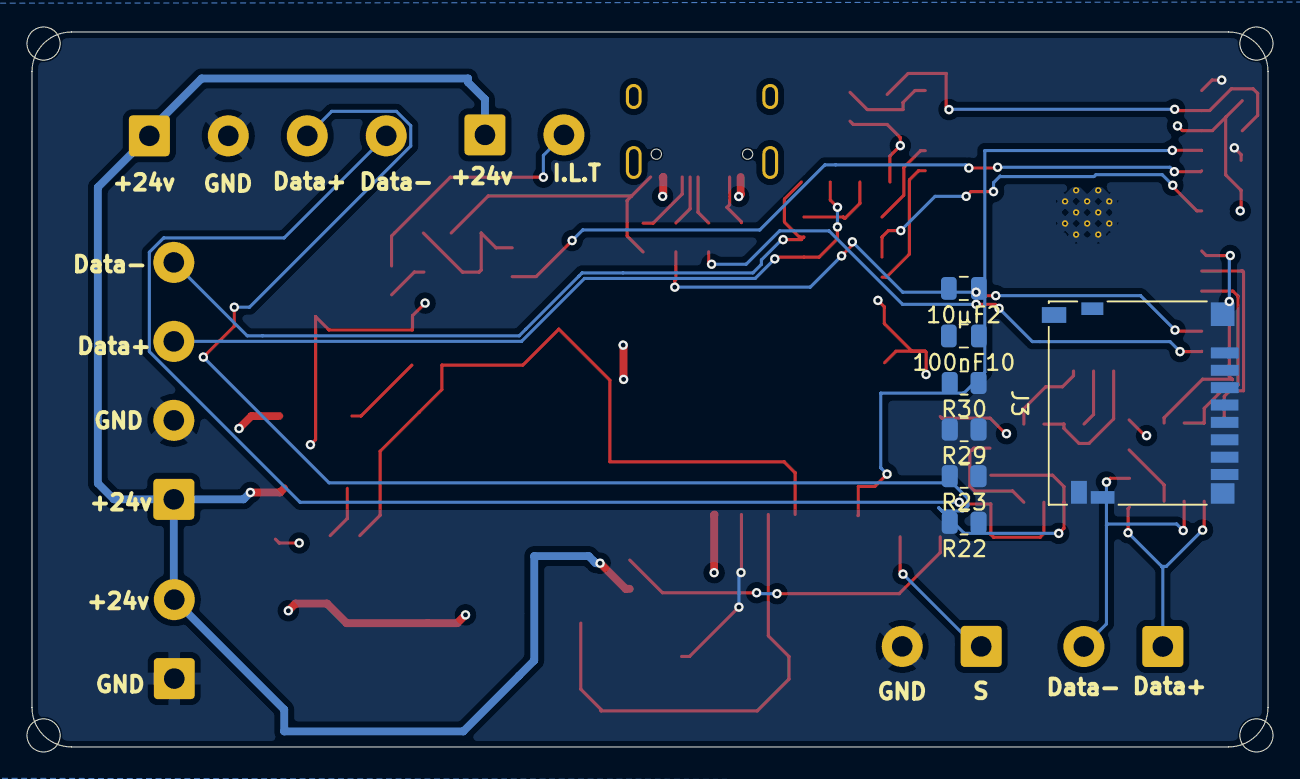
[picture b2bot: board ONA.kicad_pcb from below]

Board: 4 copper layers, 78.3 x 45.3 mm, 60 parts (7 on the bottom side), 40 nets.

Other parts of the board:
 : MountingHole_2.1mm
 #2,  #4,  #5: MountingHole_2.1mm
 #3: LOGO

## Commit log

2026-03-25 Auther: Ziad, Breif: add hardware
2026-03-26 add files
2026-05-02 add software
2026-05-02 Add browse.vc.db to gitignore
2026-05-02 stm32 files
2026-05-02 Remove .history folder and add to gitignore
2026-05-02 chore: remove .history folders and add to gitignore
2026-05-02 chore: ignore .db files
2026-05-02 init product
2026-05-02 docs: professional README with product gallery
2026-05-02 add hard v1
2026-05-03 add ota software
2026-05-09 add 3d model
2026-05-09 edit into readme file
2026-05-21 add docs
2026-06-03 Remove build artifacts and add .gitignore

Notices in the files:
README.md:
License: Proprietary
